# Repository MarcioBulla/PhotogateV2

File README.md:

# Photogate V2

[DOI: 10.5281/zenodo.22728248](https://doi.org/10.5281/zenodo.22728248)

PhotogateV2 is certified by OSHWA as **AR000006**.

[🌐 Access Photogate V2 Website](https://photogatev2.marciobulla.com/)  
[📄 View Interactive IBOM](https://photogatev2.marciobulla.com/ibom.html)

**Version 2 of the Photogate** — implemented with **ESP-IDF v5.4.2** for an ESP32-based photogate project.

---

## Overview

This is the second version of the **Photogate** project, featuring significant improvements in accuracy, reliability, and visual interface, along with available 3D models and schematics.  :
Designed for educational and experimental applications using the ESP32 platform.

---

## Requirements

- **ESP-IDF v5.4**
- A configured ESP32 development environment (terminal toolchain)
- Required cables and hardware to flash the firmware

---

## Build and Run

1. Clone the repository:
   ```bash
   git clone https://github.com/marciobulla/photogateV2.git
   cd photogateV2
   ```

2. Set up the ESP-IDF environment  
   Follow the [Get Started with ESP-IDF](https://docs.espressif.com/projects/esp-idf) guide.

3. Build, flash, and monitor:

   ```bash
   idf.py build flash monitor
   ```

   This will compile the project, upload it to your ESP32, and open the serial monitor.

---

## Repository Structure

* `firmware/` — C source code for ESP32 firmware
* `boards/` — PCB layouts or circuit schematics
* `3DModels/` — Printable or viewable 3D models of the device
* `README.md` — Project documentation (this file)
* Additional helper scripts and documentation

---

## Interactive Bill of Materials (IBOM)

Below is a preview of the Interactive BOM:

🔗 [Open Interactive IBOM](https://photogatev2.marciobulla.com/ibom.html)

---

## Credits

Developed by **Marcio Bulla**. Inspired by the first Photogate (Optical Timer) version.  
Special thanks to the libraries used in this project, such as `encoder_menu.py`, `rotary.py`, and `rotary_irq_esp.py`.

## License

PhotogateV2 uses different open-source licenses for its original contributions:

- Electronic hardware and PCB design: CERN-OHL-W-2.0
- Mechanical and 3D design: CERN-OHL-W-2.0
- PhotogateV2 firmware: Apache-2.0
- Documentation: CC-BY-SA-4.0

Third-party components retain their respective licenses. Imported assets and
materials of unresolved origin are excluded from these grants.
See [LICENSES.md](LICENSES.md) for scope and exceptions, and
[THIRD_PARTY.md](THIRD_PARTY.md) for firmware dependencies and license evidence.

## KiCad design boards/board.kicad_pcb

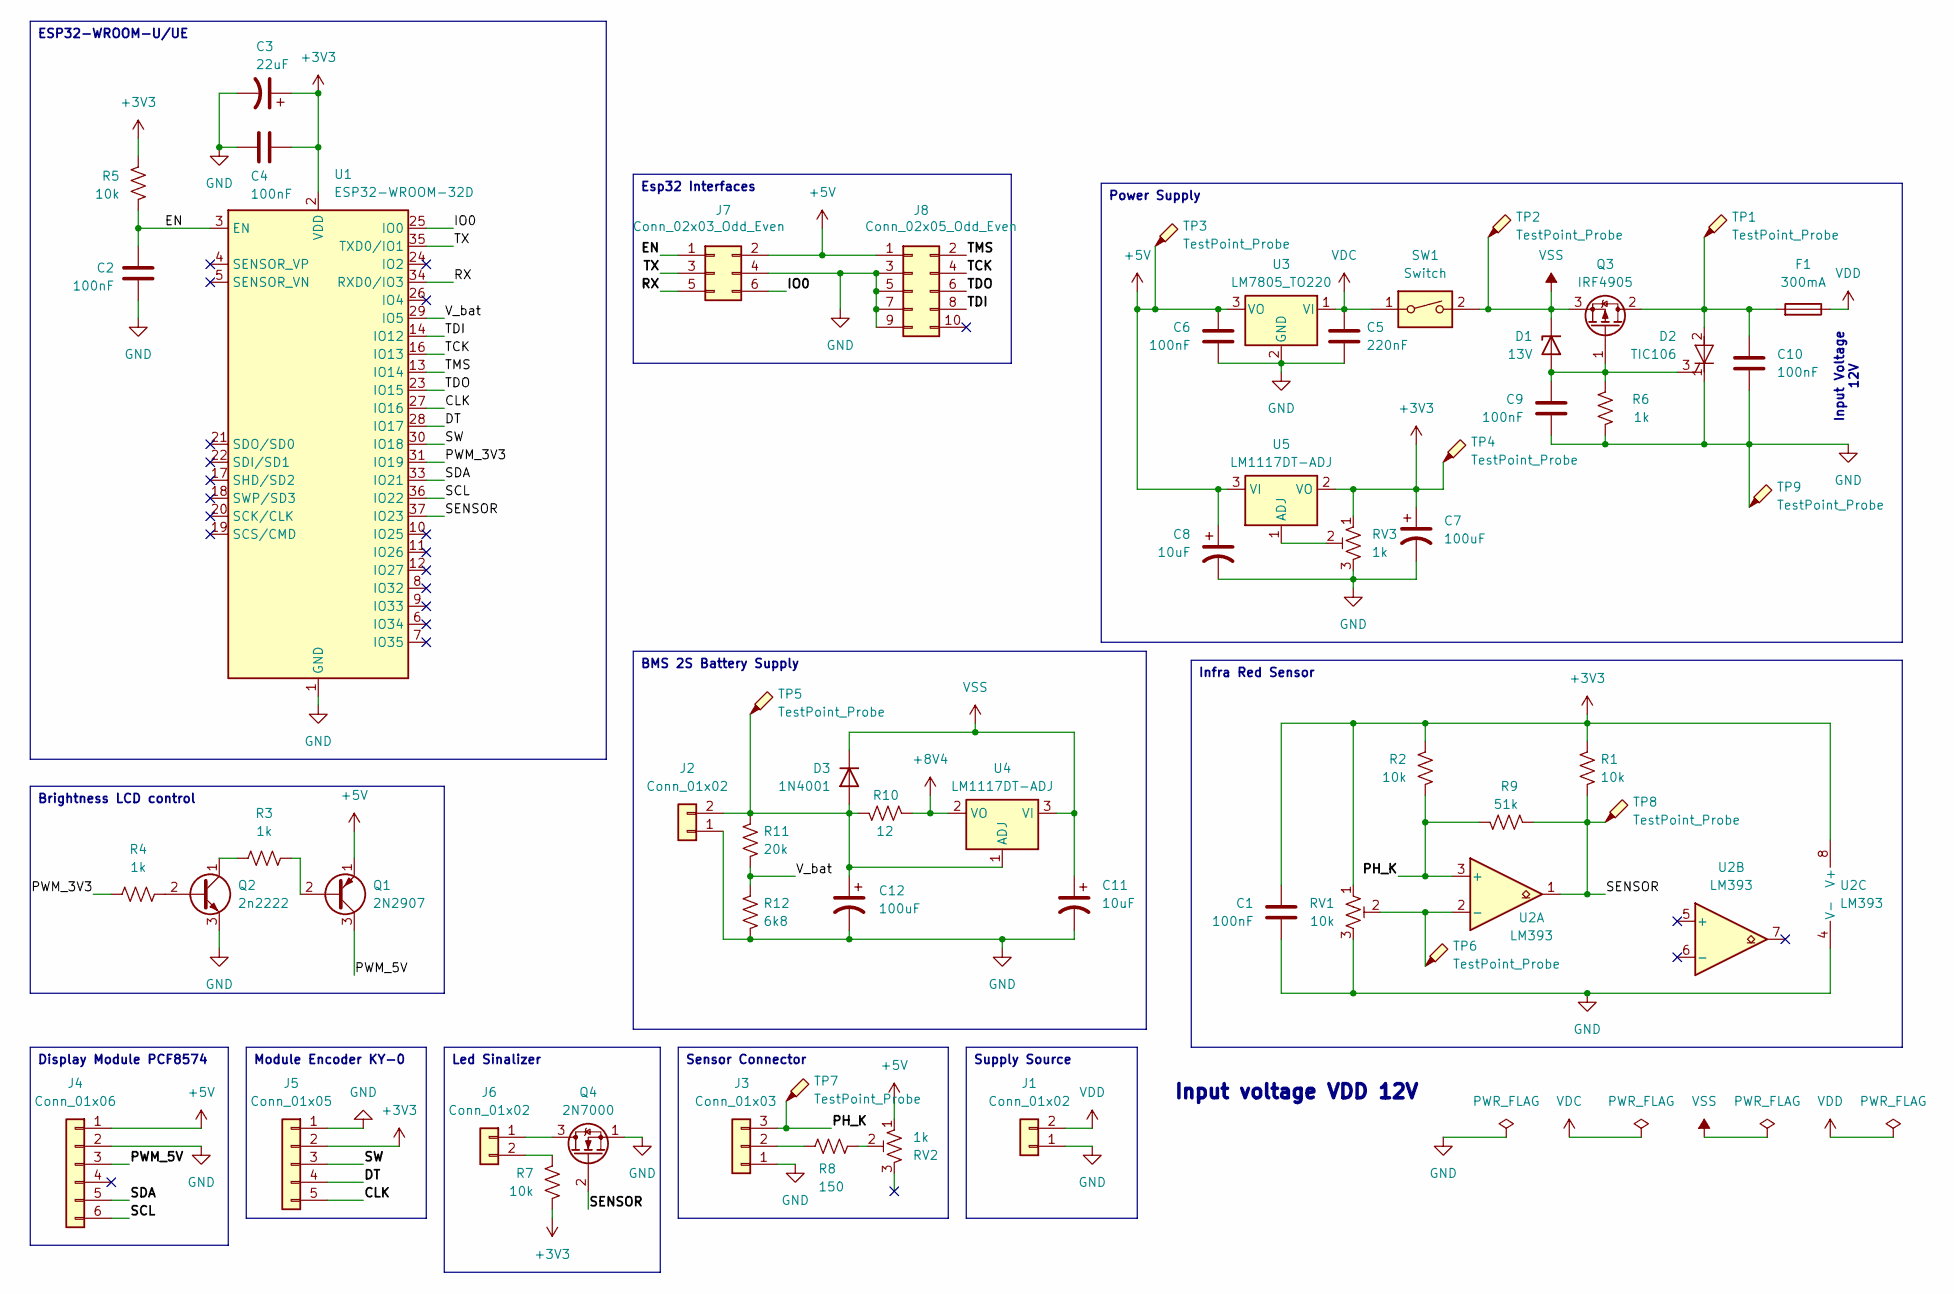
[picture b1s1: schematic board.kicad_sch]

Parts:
C1, C2, C4, C9, C10: 100nF; C_Disc_D6.0mm_W2.5mm_P5.00mm; LCSC C110254
C3: 22uF; CAP-TH_BD4.0-P1.50-D0.8-FD; LCSC C43845
C5: 220nF; C_Rect_L7.0mm_W2.5mm_P5.00mm; LCSC C125389
C6: 100nF; C_Disc_D5.0mm_W2.5mm_P5.00mm; LCSC C110254
C7, C12: 100uF; CAP-TH_BD5.0-P2.00-D0.8-FD; LCSC C165586
C8, C11: 10uF; CAP-TH_BD5.0-P2.00-D0.8-FD; LCSC C106654
D1: 13V; D_DO-35_SOD27_P7.62mm_Horizontal; LCSC C261229
D2: TIC106; TO-220-3_Vertical; LCSC C9211
D3: 1N4001; DO-41_BD2.4-L4.7-P8.70-D0.9-RD; LCSC C5359862
F1: 300mA; Molex_KK-254_AE-6410-02A_1x02_P2.54mm_Vertical; LCSC C239362
J1, J2, J6: Conn_01x02; Molex_KK-254_AE-6410-02A_1x02_P2.54mm_Vertical; LCSC C239362
J3: Conn_01x03; Molex_KK-254_AE-6410-03A_1x03_P2.54mm_Vertical; LCSC C29275
J4: Conn_01x06; Molex_KK-254_AE-6410-06A_1x06_P2.54mm_Vertical; LCSC C239366
J5: Conn_01x05; Molex_KK-254_AE-6410-05A_1x05_P2.54mm_Vertical; LCSC C239365
J7: Conn_02x03_Odd_Even; IDC-Header_2x03_P2.54mm_Vertical; LCSC C11214
J8: Conn_02x05_Odd_Even; IDC-Header_2x05_P2.54mm_Vertical; LCSC C5665
Q1: 2N2907; TO-92-3_L4.8-W3.7-P2.54-R; LCSC C358534
Q2: 2n2222; TO-92_Inline; LCSC C118536
Q3: IRF4905; TO-220-3_Vertical; LCSC C2564
Q4: 2N7000; TO-92_Inline; LCSC C9114
R1, R2, R5, R7: 10k; RES-TH_BD2.3-L6.5-P10.50-D0.5; LCSC C119347
R3, R4, R6: 1k; RES-TH_BD2.3-L6.5-P10.50-D0.5; LCSC C119324
R8: 150; RES-TH_BD2.3-L6.5-P10.50-D0.5; LCSC C385454
R9: 51k; RES-TH_BD2.3-L6.5-P10.50-D0.5; LCSC C119363
R10: 12; RES-TH_BD4.5-L11.0-P15.00-D0.7; LCSC C479307
R11: 20k; RES-TH_BD2.3-L6.5-P10.50-D0.5; LCSC C119353
R12: 6k8; RES-TH_BD2.3-L6.5-P10.50-D0.5; LCSC C714012
RV1: 10k; Potentiometer_Bourns_3386X_Horizontal; LCSC C780119
RV2, RV3: 1k; Potentiometer_Bourns_3386X_Horizontal; LCSC C780120
SW1: Switch; Molex_KK-254_AE-6410-02A_1x02_P2.54mm_Vertical; LCSC C239362
TP1, TP2, TP3, TP4, TP5, TP6, TP7, TP8, TP9: TestPoint_Probe; TestPoint_THTPad_3.0x3.0mm_Drill1.5mm
U1: ESP32-WROOM-32D; LCSC C473012
U2: LM393; DIP-8_W7.62mm; LCSC C725322
U3: LM7805_TO220; TO-220-3_Vertical; LCSC C3795
U4, U5: LM1117DT-ADJ; TO-220-3_Vertical; LCSC C498319

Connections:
+3V3: C1.1, C3.1, C4.1, C7.1, J5.2, R1.1, R2.1, R5.1, R7.1, RV1.1, RV3.1, TP4.1, U1.2 (VDD), U2.8 (V+), U5.2 (VO)
+5V: C6.1, C8.1, J4.1, J7.2, J8.1, Q1.1 (E), RV2.1, TP3.1, U3.3 (VO), U5.3 (VI)
+8V4: R10.2, U4.2 (VO)
/CLK: J5.5, U1.27 (IO16)
/DT: J5.4, U1.28 (IO17)
/EN: C2.1, J7.1, R5.2, U1.3 (EN)
/IO0: J7.6, U1.25 (IO0)
/PH_K: J3.3, R2.2, R9.1, TP7.1, U2.3 (+)
/PWM_3V3: R4.1, U1.31 (IO19)
/PWM_5V: J4.3, Q1.3 (C)
/RX: J7.5, U1.34 (RXD0/IO3)
/SCL: J4.6, U1.36 (IO22)
/SDA: J4.5, U1.33 (IO21)
/SENSOR: Q4.2 (G), R1.2, R9.2, TP8.1, U1.37 (IO23), U2.1
/SW: J5.3, U1.30 (IO18)
/TCK: J8.4, U1.16 (IO13)
/TDI: J8.8, U1.14 (IO12)
/TDO: J8.6, U1.23 (IO15)
/TMS: J8.2, U1.13 (IO14)
/TX: J7.3, U1.35 (TXD0/IO1)
/V_bat: R11.2, R12.1, U1.29 (IO5)
GND: C1.2, C2.2, C3.2, C4.2, C5.2, C6.2, C7.2, C8.2, C9.2, C10.2, C11.2, C12.2, D2.1 (K), J1.1, J2.1, J3.1, J4.2, J5.1, J7.4, J8.3, J8.5, J8.7, J8.9, Q2.3 (E), Q4.1 (S), R6.2, R12.2, RV1.3, RV3.3, TP9.1, U1.1 (GND), U1.15 (GND), U1.38 (GND), U1.39 (GND), U2.4 (V-), U3.2 (GND)
unnamed: C9.1, D1.2 (A), D2.3 (G), Q3.1 (G), R6.1
unnamed: C10.1, D2.2 (A), F1.2, Q3.2 (D), TP1.1
unnamed: C12.1, D3.2 (A), J2.2, R10.1, R11.1, TP5.1, U4.1 (ADJ)
unnamed: J3.2, R8.1
unnamed: J6.1, Q4.3 (D)
unnamed: J6.2, R7.2
unnamed: Q1.2 (B), R3.2
unnamed: Q2.2 (B), R4.2
unnamed: Q2.1 (C), R3.1
unnamed: R8.2, RV2.2
unnamed: RV1.2, TP6.1, U2.2 (-)
unnamed: RV3.2, U5.1 (ADJ)
VDC: C5.1, SW1.1, U3.1 (VI)
VDD: F1.1, J1.2
VSS: C11.1, D1.1 (K), D3.1 (K), Q3.3 (S), SW1.2, TP2.1, U4.3 (VI)

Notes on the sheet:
Input Voltage 12V
Input voltage VDD 12V
ESP32-WROOM-U/UE
Esp32 Interfaces
Infra Red Sensor
Supply Source
Power Supply
Module Encoder KY-0
BMS 2S Battery Supply
Led Sinalizer
Brightness LCD control
Sensor Connector
Display Module PCF8574

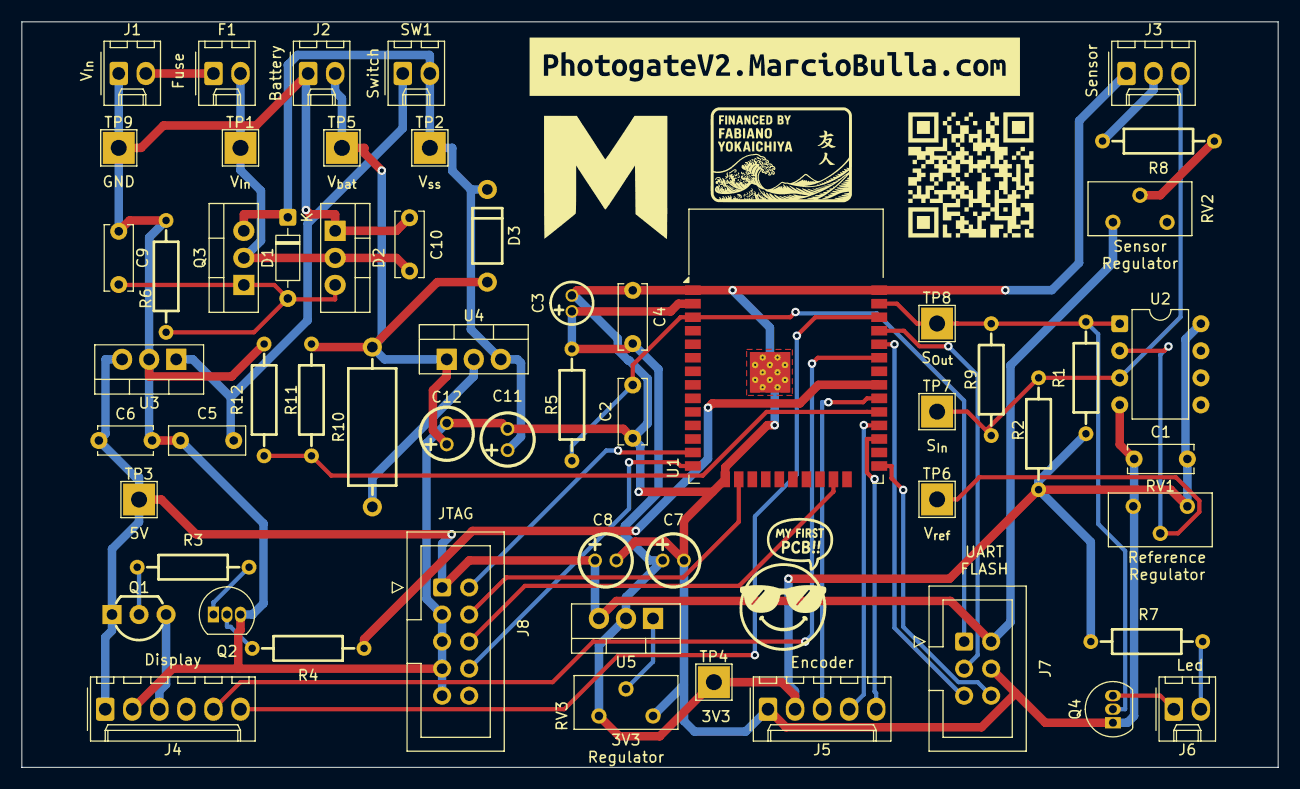
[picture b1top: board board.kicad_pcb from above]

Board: 2 copper layers, 118.0 x 70.0 mm, 61 parts (0 on the bottom side), 37 nets.

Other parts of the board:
QRcode git: LOGO3; LOGO
kibuzzard-689E6D12: G***; kibuzzard-689E6D12
kibuzzard-689E6DF9: G***; kibuzzard-689E6DF9

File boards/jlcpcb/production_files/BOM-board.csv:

Comment,Designator,Footprint,LCSC,Quantity
10uF,"C11,C8",CAP-TH_BD5.0-P2.00-D0.8-FD,C106654,2
100nF,"C1,C10,C2,C4,C6,C9",C_Disc_D6.0mm_W2.5mm_P5.00mm,C110254,6
Conn_02x03_Odd_Even,J7,IDC-Header_2x03_P2.54mm_Vertical,C11214,1
2n2222,Q2,TO-92_Inline,C118536,1
1k,"R3,R4,R6",RES-TH_BD2.3-L6.5-P10.50-D0.5,C119324,3
10k,"R1,R2,R5,R7",RES-TH_BD2.3-L6.5-P10.50-D0.5,C119347,4
20k,R11,RES-TH_BD2.3-L6.5-P10.50-D0.5,C119353,1
51k,R9,RES-TH_BD2.3-L6.5-P10.50-D0.5,C119363,1
220nF,C5,C_Rect_L7.0mm_W2.5mm_P5.00mm,C125389,1
100uF,"C12,C7",CAP-TH_BD5.0-P2.00-D0.8-FD,C165586,2
300mA,"F1,J1,J2,J6,SW1",Molex_KK-254_AE-6410-02A_1x02_P2.54mm_Vertical,C239362,5
Conn_01x05,J5,Molex_KK-254_AE-6410-05A_1x05_P2.54mm_Vertical,C239365,1
Conn_01x06,J4,Molex_KK-254_AE-6410-06A_1x06_P2.54mm_Vertical,C239366,1
IRF4905,Q3,TO-220-3_Vertical,C2564,1
13V,D1,D_DO-35_SOD27_P7.62mm_Horizontal,C261229,1
Conn_01x03,J3,Molex_KK-254_AE-6410-03A_1x03_P2.54mm_Vertical,C29275,1
2N2907,Q1,TO-92-3_L4.8-W3.7-P2.54-R,C358534,1
LM7805_TO220,U3,TO-220-3_Vertical,C3795,1
150,R8,RES-TH_BD2.3-L6.5-P10.50-D0.5,C385454,1
22uF,C3,CAP-TH_BD4.0-P1.50-D0.8-FD,C43845,1
ESP32-WROOM-32D,U1,ESP32-WROOM-32D,C473012,1
12,R10,RES-TH_BD4.5-L11.0-P15.00-D0.7,C479307,1
LM1117DT-ADJ,"U4,U5",TO-220-3_Vertical,C498319,2
1N4001,D3,DO-41_BD2.4-L4.7-P8.70-D0.9-RD,C5359862,1
Conn_02x05_Odd_Even,J8,IDC-Header_2x05_P2.54mm_Vertical,C5665,1
6k8,R12,RES-TH_BD2.3-L6.5-P10.50-D0.5,C714012,1
LM393,U2,DIP-8_W7.62mm,C725322,1
10k,RV1,Potentiometer_Bourns_3386X_Horizontal,C780119,1
1k,"RV2,RV3",Potentiometer_Bourns_3386X_Horizontal,C780120,2
2N7000,Q4,TO-92_Inline,C9114,1
TIC106,D2,TO-220-3_Vertical,C9211,1

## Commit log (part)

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2024-02-13 pedulumn, info done
2024-02-15 add filter glitch
2024-02-16 add spring and Mecanical Energy
2024-02-21 create and improve prin to display
2024-02-22 save menutype flash
2024-02-23 First Final Version (withoutcomments)
2024-02-23 bug correction
2024-02-24 add comments
2024-02-25 ajust comments and a little bit improve code
2024-03-03 Init Modeling
2024-03-06 Schematic almost done
2024-03-12 correct error Sensor obstructed
2024-03-12 aded unnecessary files from KiaCAD and FreeCAD
2024-03-12 creating board
2024-04-13 Improve model
2024-04-15 3D Model Complete
2024-04-15 improve thumbscrew
2024-04-19 ajust sensor circuit
2024-05-03 Bug obstructed sensor end measuring lost
2024-05-03 create EXPERIMENT_ERROR to correct batter obstructed
2024-05-04 Improve obsructed sensor
2024-05-04 add hysteresis on sensor
2024-05-04 organize schematic
2024-09-17 Fix model
2024-09-17 Fix schematic
2024-09-17 improve arm and add screw
2024-09-22 add battery support
2024-09-25 ajust holes of BOX
2025-07-14 Refactor firmware photagate
2025-07-14 Remove unnecessary Git submodules
2025-07-15 Minimal instruction
2025-07-21 align time on history
2025-08-12 create pcb and update circuit
2025-08-14 update PCB and create gerber
2025-08-14 change color
2025-08-14 add Interactive bom
2025-08-14 Create CNAME
2025-08-14 Update CNAME
2025-08-14 remove iframe
2025-08-14 create simple docs
2025-08-14 fix iframe
2025-08-14 fix iframe again
2025-08-14 sync theme ibom and page
2025-08-14 ajust version
2025-08-14 Ajust J7 component
2025-08-14 update ibom
2025-08-14 update docs
2025-08-14 update ibom and apply backgroud 3dmodel
2025-08-14 Ajust Caracteristic card title
2025-08-15 Fiz positon components, add Fabiano seal
2025-08-15 Remove SW
2025-08-15 Update board's 3d model
2025-08-16 add B.Silkscreen to conn pins
2025-08-30 add site link in INFO
2025-08-30 Redrawing 3Dmodel
2025-09-01 all case modelated
2025-09-01 assambled
2025-09-02 assambly and export new case
2025-09-02 add stand for case and create sensor
2025-09-03 add angle in stand and ajust box
2025-09-04 improve cable conduit of IrSensor
2025-09-04 add nuts space in box
2025-09-04 simplifying knobs
2025-09-07 add space for baterry
2025-09-09 reforc2Arm Lorxi's logo in (Knob -> ThumbScrew)
2025-09-09 add Knob
2025-09-09 align stand and box
2025-09-11 remove blink display when start
2025-09-14 add support bracket for arm
2025-09-22 little ajust on Thumbscrew to add a nuts
2025-10-29 add sensor assembled
2025-10-31 clear queue in done's stage
2025-10-31 add clip on IR sesnor
2026-04-02 fix print time on cronos.c
2026-04-02 remove unecessary minor version of ESP-IDF
2026-04-02 save kicad_pro in kicad 10
2026-04-12 reconfigure model to FreeCAD 1.1
2026-04-12 remove minor version of esp-idf version
2026-04-13 create and implement new config min pulse width
2026-04-19 rename modules in sketch
2026-04-19 rename again modules in sketch
2026-05-27 docs: reorganize project documentation site
